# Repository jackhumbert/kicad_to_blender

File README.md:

This is an example to walkthrough a KiCAD to Blender workflow for creating renders of PCBs. I'm using Blender 2.81.16 and KiCAD (5.1.5)-3, but I don't think anything here is specific to these versions. The KiCAD file is pretty much entirely junk - nothing here is wired or routed up correctly like you would for an actual PCB.

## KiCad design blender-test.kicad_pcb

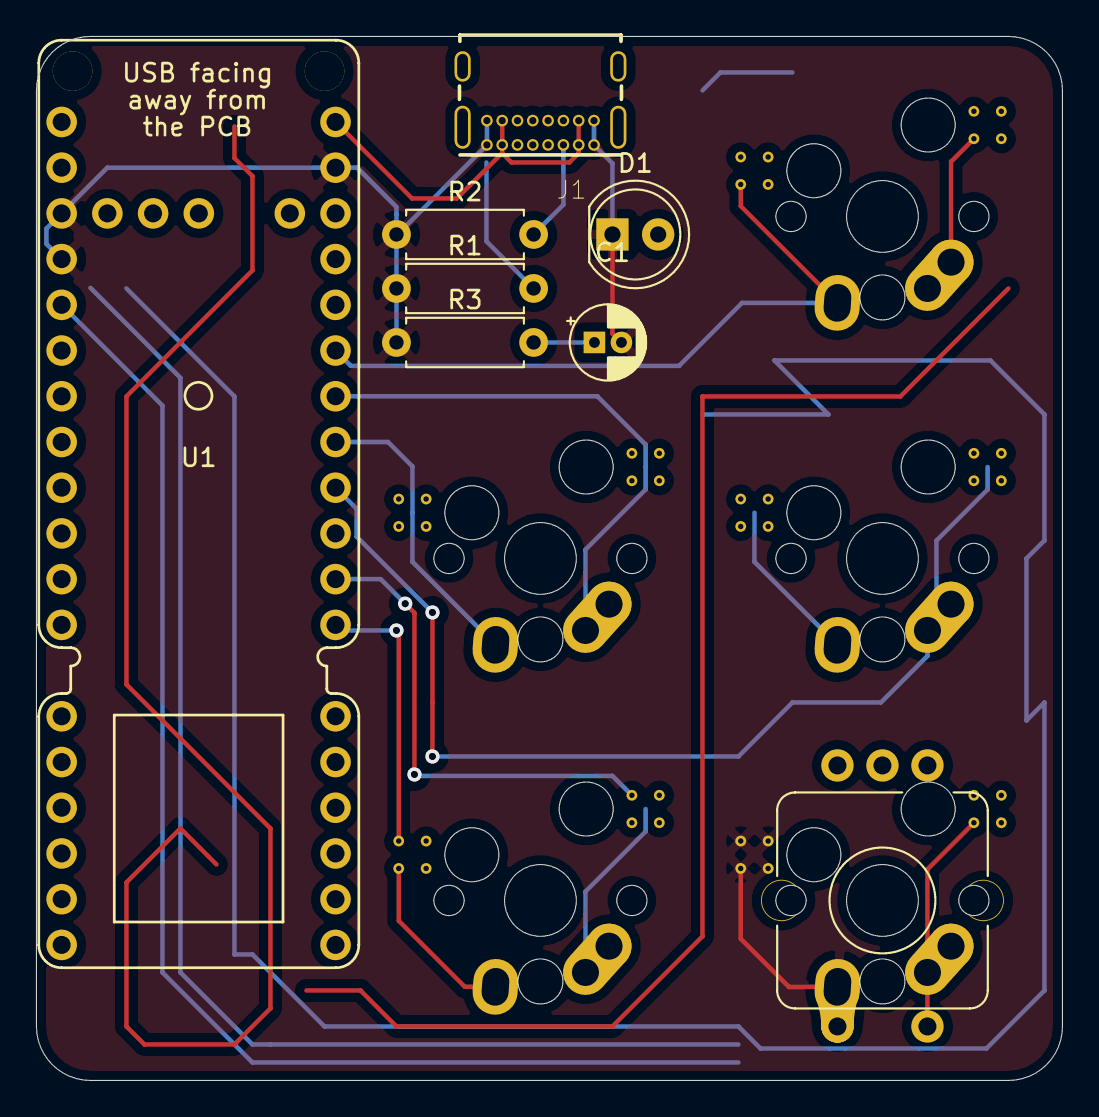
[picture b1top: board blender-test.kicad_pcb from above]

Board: 2 copper layers, 57.0 x 58.0 mm, 12 parts (0 on the bottom side), 15 nets.

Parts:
C1: C; CP_Radial_D4.0mm_P1.50mm
D1: LED; LED_D5.0mm
J1: USB4085-GF-A_REVA; GCT_USB4085-GF-A_REVA
R1, R2: 5k1; R_Axial_DIN0207_L6.3mm_D2.5mm_P7.62mm_Horizontal
R3: R; R_Axial_DIN0207_L6.3mm_D2.5mm_P7.62mm_Horizontal
SW1, SW2, SW3, SW4: Switch; UniKBSwitch_1u-kailk-socket-matis-mx-rgb-circle-2.5-vias
SW5: Rotary_Encoder_Switch; UniKBSwitch_1u-kailk-socket-matis-mx-rgb-circle-2.5-vias-en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
U1: proton_c

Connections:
GND: C1.2, D1.1, J1.A1, J1.A12, J1.B1, J1.B12, R1.1, R2.1, R3.1, SW5.2, U1.GND
unnamed: C1.1, J1.P1, J1.P2, J1.P3, J1.P4, R3.2
unnamed: J1.A4, J1.A9, J1.B4, J1.B9, U1.5V
unnamed: J1.A5, R2.2
unnamed: J1.A6, J1.B6, U1.D+
unnamed: J1.A7, J1.B7, U1.D-
unnamed: J1.B5, R1.2
unnamed: SW1.1, U1.A2
unnamed: SW1.2, U1.A1
unnamed: SW2.1, U1.A0
unnamed: SW2.2, U1.B8
unnamed: SW3.1, U1.B13
unnamed: SW3.2, U1.B14
unnamed: SW4.1, U1.B15
unnamed: SW4.2, U1.B9

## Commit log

2020-01-01 Create LICENSE
2020-01-01 add files
